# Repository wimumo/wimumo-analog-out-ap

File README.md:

# wimumo-analog-out-ap

Complemento receptor para WIMUMO

Este proyecto de Arduino implementa un receptor de los mensajes de WIMUMO en el ESP32 utilizando el protocolo OSC sobre UDP. Los mensajes se obtienen de los Bundles OSC recibidos, se acondicionan para la salida PWM de 10 bits y adicionalmente se envían por el puerto serie.

## Instalación

Todo está hecho en el entorno de Arduino. Deben instalarse algunas librerías para programar el ESP32 y funcionalidad como servidor.

### Tarjeta de ESP32

Para que aparezca la "tarjeta": En Archivo -> preferencias -> gestores adicionales agregar la fuente https://raw.githubusercontent.com/espressif/arduino-esp32/gh-pages/package_esp32_index.json   

Se seleccionó placa WEMOS D1 MINI ESP32

### Librerías del proyecto: 

- https://github.com/me-no-dev/ESPAsyncWebServer (descargar y descomprimir en Program Files/Arduino/libraries)

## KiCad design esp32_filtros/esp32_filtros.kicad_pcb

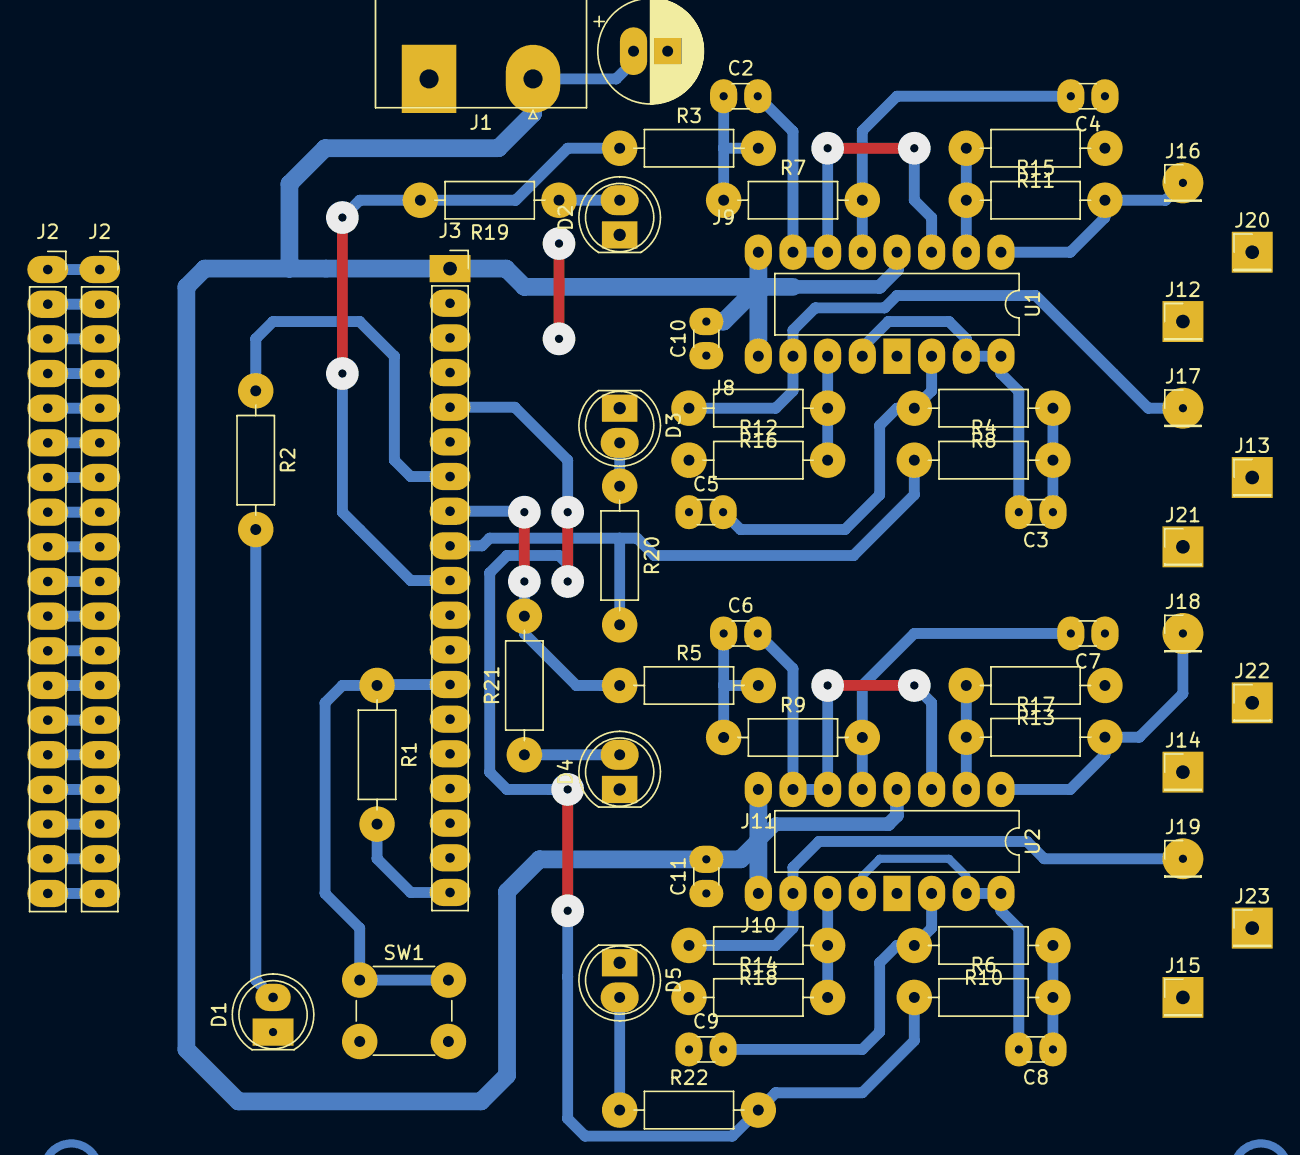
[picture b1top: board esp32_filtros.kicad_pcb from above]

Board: 2 copper layers, 61 parts (0 on the bottom side), 53 nets.

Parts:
C1: CP; CP_Radial_D7.5mm_P2.50mm
C2, C3, C4, C5, C6, C7, C8, C9, C10, C11: C; C_Disc_D3.0mm_W1.6mm_P2.50mm
D1, D2, D3, D4, D5: LED; LED_D5.0mm
J1: alimentación; PhoenixContact_GMSTBA_2,5_2-G-7,62_1x02_P7.62mm_Horizontal
J2, J2#2: esp32-1; PinSocket_1x19_P2.54mm_Vertical
J3: esp32-2; PinSocket_1x19_P2.54mm_Vertical
J8, J9: 8&9 IC-1; PinHeader_1x01_P2.54mm_Vertical
J10, J11: 8&9 IC-2; PinHeader_1x01_P2.54mm_Vertical
J12, J13, J14, J15, J16, J17, J18, J19, J20, J21, J22, J23: Conn_01x01_Female; PinHeader_1x01_P2.54mm_Vertical
R1, R2, R3, R4, R5, R6, R7, R8, R9, R10, R11, R12, R13, R14, R15, R16, R17, R18, R19, R20, R21, R22: R; R_Axial_DIN0207_L6.3mm_D2.5mm_P10.16mm_Horizontal
SW1: SW_Push; SW_PUSH_6mm_H4.3mm
U1, U2: LM324; DIP-14_W7.62mm_LongPads

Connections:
+5V: C1.1, C10.2, C11.2, J1.1, J3.1, J8.1, J9.1, J10.1, J11.1, U1.4, U2.4
GND: C1.2, C4.1, C5.1, C7.1, C9.1, C10.1, C11.1, D1.1, D2.1, D3.1, D4.1, D5.1, J1.2, J3.6, J12.1, J13.1, J14.1, J15.1, J20.1, J21.1, J22.1, J23.1, R11.1, R12.1, R13.1, R14.1, SW1.2, U1.11, U2.11
unnamed: C2.1, R3.2, R7.1
unnamed: C2.2, U1.3, U1.6, U1.7
unnamed: C3.1, R4.2, R8.1
unnamed: C3.2, U1.10, U1.13, U1.14
unnamed: C4.2, R7.2, U1.5
unnamed: C5.2, R8.2, U1.12
unnamed: C6.1, R5.2, R9.1
unnamed: C6.2, U2.3, U2.6, U2.7
unnamed: C7.2, R9.2, U2.5
unnamed: C8.1, R6.2, R10.1
unnamed: C8.2, U2.10, U2.13, U2.14
unnamed: C9.2, R10.2, U2.12
unnamed: D1.2, R2.2
unnamed: D2.2, R19.1
unnamed: D3.2, R20.1
unnamed: D4.2, R21.1
unnamed: D5.2, R22.1
unnamed: J2.1, J2#2.1
unnamed: J2.2, J2#2.2
unnamed: J2.3, J2#2.3
unnamed: J2.4, J2#2.4
unnamed: J2.5, J2#2.5
unnamed: J2.6, J2#2.6
unnamed: J2.7, J2#2.7
unnamed: J2.8, J2#2.8
unnamed: J2.9, J2#2.9
unnamed: J2.10, J2#2.10
unnamed: J2.11, J2#2.11
unnamed: J2.12, J2#2.12
unnamed: J2.13, J2#2.13
unnamed: J2.14, J2#2.14
unnamed: J2.15, J2#2.15
unnamed: J2.16, J2#2.16
unnamed: J2.17, J2#2.17
unnamed: J2.18, J2#2.18
unnamed: J2.19, J2#2.19
unnamed: J3.5, R6.1, R22.2
unnamed: J3.7, R2.1
unnamed: J3.8, R5.1, R21.2
unnamed: J3.9, R4.1, R20.2
unnamed: J3.10, R3.1, R19.2
unnamed: J3.13, R1.1, SW1.1
unnamed: J3.19, R1.2
unnamed: J16.1, R15.2, U1.1
unnamed: J17.1, R16.2, U1.8
unnamed: J18.1, R17.2, U2.1
unnamed: J19.1, R18.2, U2.8
unnamed: R11.2, R15.1, U1.2
unnamed: R12.2, R16.1, U1.9
unnamed: R13.2, R17.1, U2.2
unnamed: R14.2, R18.1, U2.9

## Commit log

2023-09-06 valores val1, val2 inicializados
2023-09-06 agregado circuito KiCad
2023-09-06 agregado pdf
